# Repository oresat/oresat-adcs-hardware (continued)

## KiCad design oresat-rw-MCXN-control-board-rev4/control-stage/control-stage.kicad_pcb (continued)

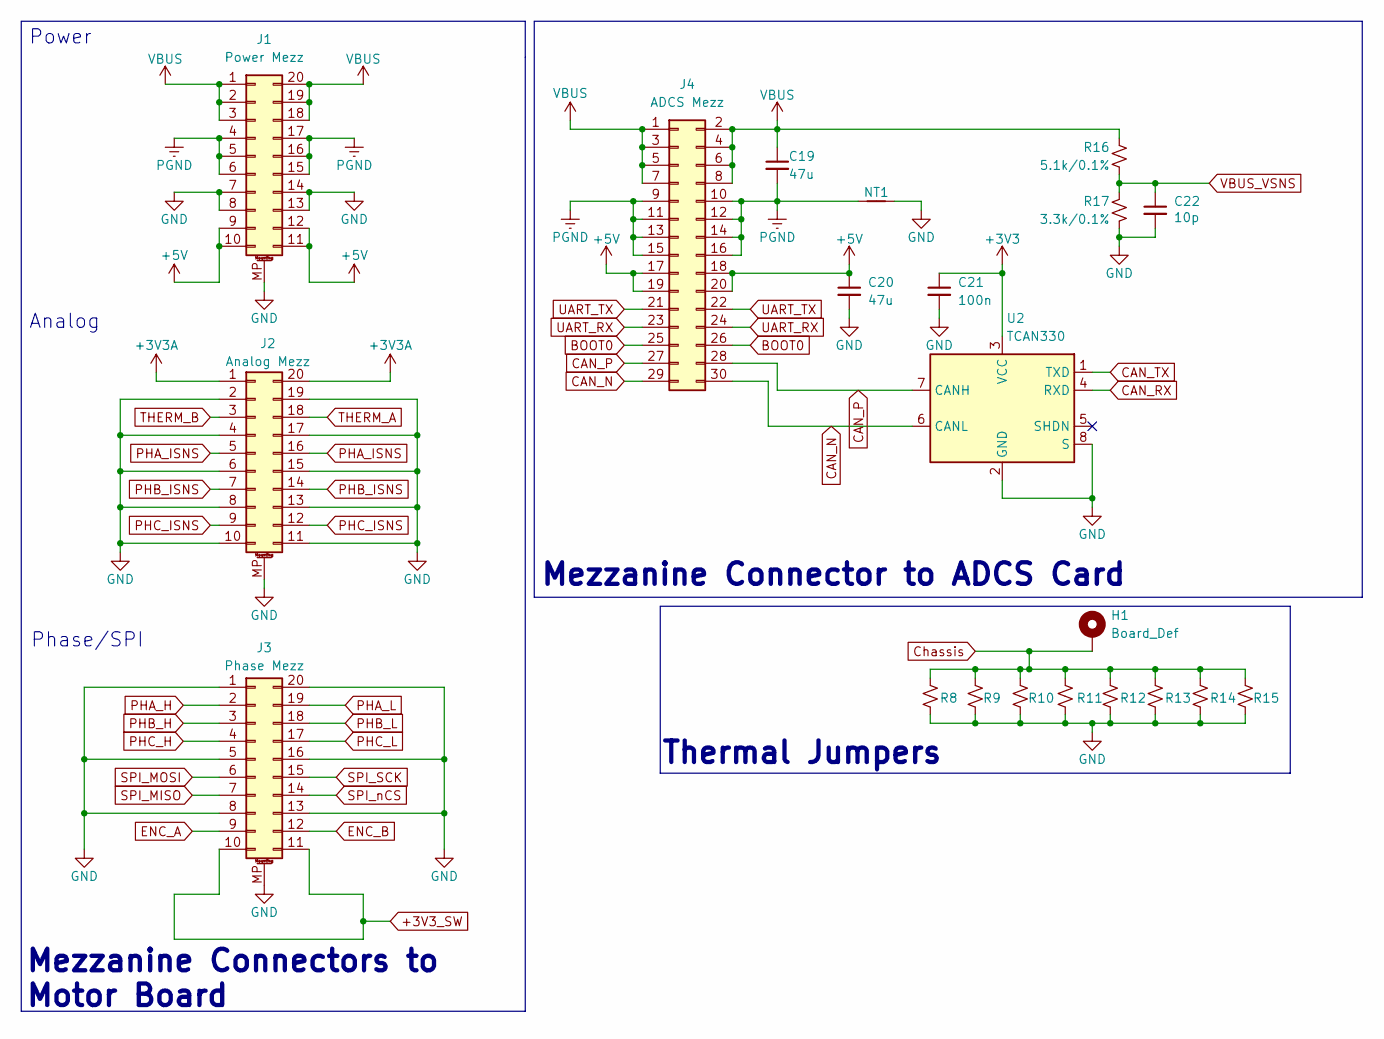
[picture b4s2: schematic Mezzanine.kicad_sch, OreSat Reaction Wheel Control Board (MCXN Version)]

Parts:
C19, C20: 47u; C_1210_3225Metric; Mfg P/N GRM32ER71A476KE15L
C21: 100n; C_0402_1005Metric; Mfg P/N GRM155R61A104KA01J
C22: 10p; C_0402_1005Metric; Mfg P/N GRM1555C1H100JA01D
H1: Board_Def; top-board-def-rev7.1
J1: Power Mezz; 10132798-021100LF; Mfg P/N 10132798-021100LF
J2: Analog Mezz; 10132798-021100LF; Mfg P/N 10132798-021100LF
J3: Phase Mezz; 10132798-021100LF; Mfg P/N 10132798-021100LF
J4: ADCS Mezz; 0555600307; Mfg P/N 555600307
NT1: NetTie; NetTie_ADCS
R8, R9, R10, R11, R12, R13, R14, R15: THJP1206ABT1; R_1206_3216Metric; Mfg P/N THJP1206ABT1
R16: 5.1k/0.1%; R_0402_1005Metric; Mfg P/N RP0402BRD075K1L
R17: 3.3k/0.1%; R_0402_1005Metric; Mfg P/N RP0402BRD073K3L
U2: TCAN330; SOT-23-8-Fixed; Mfg P/N TCAN330DCNR

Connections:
+3V3: C21.1, U2.3 (VCC); also elsewhere on the board
+3V3A: J2.1, J2.20; also elsewhere on the board
+3V3_SW: J3.10, J3.11; also elsewhere on the board
+5V: C20.1, J1.9, J1.10, J1.11, J1.12, J4.17, J4.18, J4.19, J4.20; also elsewhere on the board
BOOT0: J4.25, J4.26; also elsewhere on the board
CAN_N: J4.29, J4.30, U2.6 (CANL)
CAN_P: J4.27, J4.28, U2.7 (CANH)
CAN_RX: U2.4 (RXD); also elsewhere on the board
CAN_TX: U2.1 (TXD); also elsewhere on the board
Chassis: H1.1, R8.1, R9.1, R10.1, R11.1, R12.1, R13.1, R14.1, R15.1
ENC_A: J3.9; also elsewhere on the board
ENC_B: J3.12; also elsewhere on the board
GND: C20.2, C21.2, C22.2, J1.7, J1.8, J1.13, J1.14, J1.MP (MountPin), J2.2, J2.4, J2.6, J2.8, J2.10, J2.11, J2.13, J2.15, J2.17, J2.19, J2.MP (MountPin), J3.1, J3.5, J3.8, J3.13, J3.16, J3.20, J3.MP (MountPin), NT1.2, R8.2, R9.2, R10.2, R11.2, R12.2, R13.2, R14.2, R15.2, R17.1, U2.2 (GND), U2.8 (S); also elsewhere on the board
PGND: C19.2, J1.4, J1.5, J1.6, J1.15, J1.16, J1.17, J4.9, J4.10, J4.11, J4.12, J4.13, J4.14, J4.15, J4.16, NT1.1
PHA_H: J3.2; also elsewhere on the board
PHA_ISNS: J2.5, J2.16; also elsewhere on the board
PHA_L: J3.19; also elsewhere on the board
PHB_H: J3.3; also elsewhere on the board
PHB_ISNS: J2.7, J2.14; also elsewhere on the board
PHB_L: J3.18; also elsewhere on the board
PHC_H: J3.4; also elsewhere on the board
PHC_ISNS: J2.9, J2.12; also elsewhere on the board
PHC_L: J3.17; also elsewhere on the board
SPI_MISO: J3.7; also elsewhere on the board
SPI_MOSI: J3.6; also elsewhere on the board
SPI_SCK: J3.15; also elsewhere on the board
SPI_nCS: J3.14; also elsewhere on the board
THERM_A: J2.18; also elsewhere on the board
THERM_B: J2.3; also elsewhere on the board
UART_RX: J4.23, J4.24; also elsewhere on the board
UART_TX: J4.21, J4.22; also elsewhere on the board
VBUS: C19.1, J1.1, J1.2, J1.3, J1.18, J1.19, J1.20, J4.1, J4.2, J4.3, J4.4, J4.5, J4.6, J4.7, J4.8, R16.1
VBUS_VSNS: C22.1, R16.2, R17.2; also elsewhere on the board

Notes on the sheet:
Power
Mezzanine Connector to ADCS Card
Thermal Jumpers
Phase/SPI
Analog
Mezzanine Connectors to Motor Board

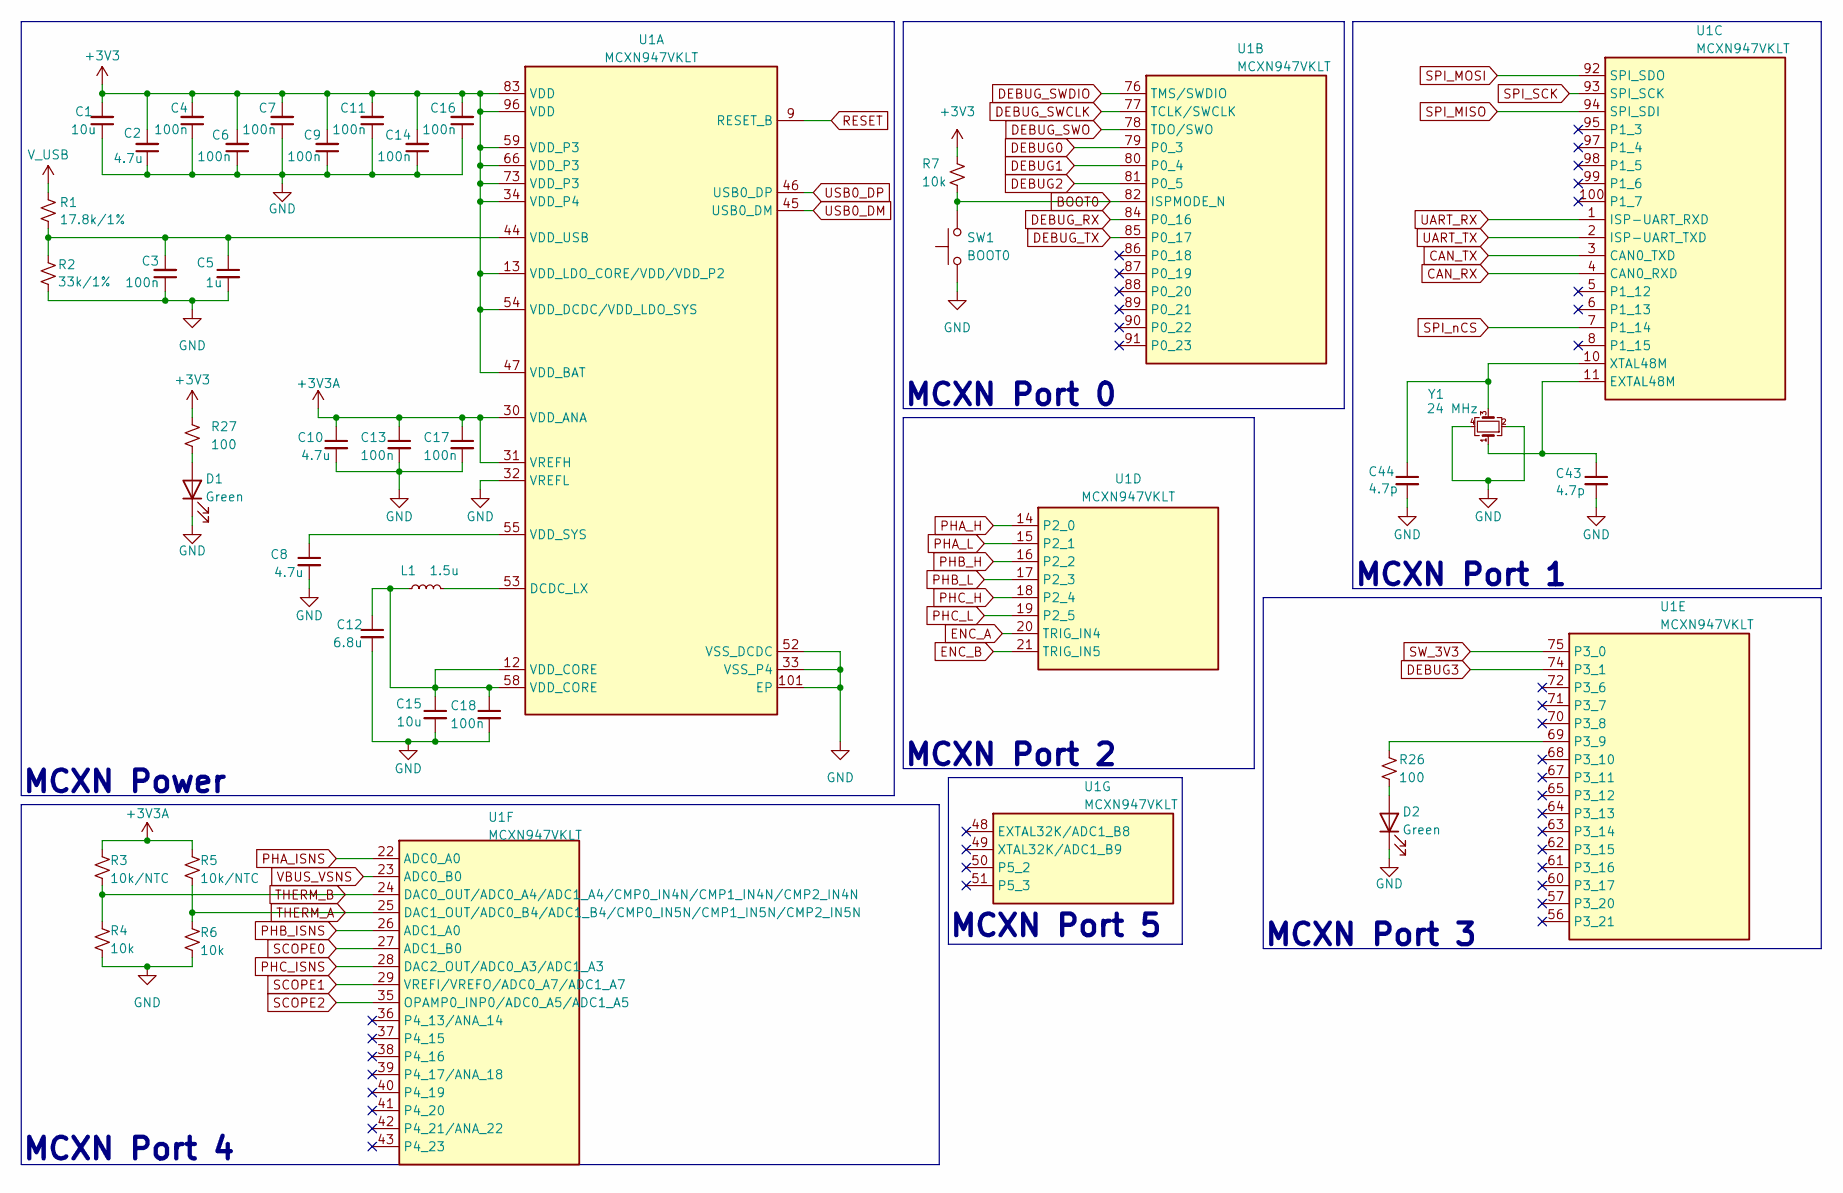
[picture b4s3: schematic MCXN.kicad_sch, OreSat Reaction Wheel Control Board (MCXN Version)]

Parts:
C1, C15: 10u; C_0603_1608Metric; Mfg P/N GRM188R61A106KE69J
C2, C8, C10: 4.7u; C_0603_1608Metric; Mfg P/N GRM185R61A475KE11D
C3, C4, C6, C7, C9, C11, C13, C14, C16, C17, C18: 100n; C_0402_1005Metric; Mfg P/N GRM155R61A104KA01J
C5: 1u; C_0402_1005Metric; Mfg P/N GRT155R61A105KE01D
C12: 6.8u; C_1206_3216Metric; Mfg P/N CGA5L1X7R1C685M160AC
C43, C44: 4.7p; 0603-C-NOSILK; MPN GRM1885C1H4R7WA01D
D1, D2: Green; LED_0603_1608Metric; Mfg P/N 150060VS55040
L1: 1.5u; L_0805_2012Metric; MPN SRP2012TMA-1R5M
R1: 17.8k/1%; R_0603_1608Metric; Mfg P/N ERJ-UP3F1782V
R2: 33k/1%; R_0603_1608Metric; Mfg P/N ERJ-UP3F3302V
R3, R5: 10k/NTC; R_0402_1005Metric; Mfg P/N NCU15XH103F6SRC
R4, R6, R7: 10k; R_0402_1005Metric; Mfg P/N AC0402DR-0710KL
R26, R27: 100; R_0402_1005Metric; Mfg P/N SR0402FR-7T100RL
SW1: BOOT0; SW_Push_SPST_NO_Alps_SKRK; Mfg P/N SKRKAGE020
U1: MCXN947VKLT; MCXN947KVLT-QFP50P1600X1600X160-101N; MPN MCXN947VKLT
Y1: 24 MHz; Crystal_SMD_2016-4Pin_2.0x1.6mm; MPN 830108212309

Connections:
+3V3: C1.2, C2.2, C4.2, C6.2, C7.2, C9.2, C11.2, C14.2, C16.2, R7.1, R27.1, U1.13 (VDD_LDO_CORE/VDD/VDD_P2), U1.34 (VDD_P4), U1.47 (VDD_BAT), U1.54 (VDD_DCDC/VDD_LDO_SYS), U1.59 (VDD_P3), U1.66 (VDD_P3), U1.73 (VDD_P3), U1.83 (VDD), U1.96 (VDD); also elsewhere on the board
+3V3A: C10.1, C13.1, C17.1, R3.1, R5.1, U1.30 (VDD_ANA), U1.31 (VREFH); also elsewhere on the board
BOOT0: R7.2, SW1.2, U1.82 (ISPMODE_N); also elsewhere on the board
CAN_RX: U1.4 (CAN0_RXD); also elsewhere on the board
CAN_TX: U1.3 (CAN0_TXD); also elsewhere on the board
DEBUG0: U1.79 (P0_3); also elsewhere on the board
DEBUG1: U1.80 (P0_4); also elsewhere on the board
DEBUG2: U1.81 (P0_5); also elsewhere on the board
DEBUG3: U1.74 (P3_1); also elsewhere on the board
DEBUG_RX: U1.84 (P0_16); also elsewhere on the board
DEBUG_SWCLK: U1.77 (TCLK/SWCLK); also elsewhere on the board
DEBUG_SWDIO: U1.76 (TMS/SWDIO); also elsewhere on the board
DEBUG_SWO: U1.78 (TDO/SWO); also elsewhere on the board
DEBUG_TX: U1.85 (P0_17); also elsewhere on the board
ENC_A: U1.20 (TRIG_IN4); also elsewhere on the board
ENC_B: U1.21 (TRIG_IN5); also elsewhere on the board
GND: C1.1, C2.1, C3.1, C4.1, C5.2, C6.1, C7.1, C8.2, C9.1, C10.2, C11.1, C12.2, C13.2, C14.1, C15.2, C16.1, C17.2, C18.2, C43.2, C44.2, D1.1 (K), D2.1 (K), R2.1, R4.2, R6.2, SW1.1, U1.32 (VREFL), U1.33 (VSS_P4), U1.52 (VSS_DCDC), U1.101 (EP), Y1.2, Y1.4; also elsewhere on the board
unnamed: C12.1, C15.1, C18.1, L1.1, U1.12 (VDD_CORE), U1.58 (VDD_CORE)
unnamed: D1.2 (A), R27.2
unnamed: D2.2 (A), R26.2
unnamed: L1.2, U1.53 (DCDC_LX)
unnamed: C8.1, U1.55 (VDD_SYS)
unnamed: C3.2, C5.1, R1.1, R2.2, U1.44 (VDD_USB)
unnamed: C44.1, U1.10 (XTAL48M), Y1.3
unnamed: C43.1, U1.11 (EXTAL48M), Y1.1
unnamed: R26.1, U1.69 (P3_9)
PHA_H: U1.14 (P2_0); also elsewhere on the board
PHA_ISNS: U1.22 (ADC0_A0); also elsewhere on the board
PHA_L: U1.15 (P2_1); also elsewhere on the board
PHB_H: U1.16 (P2_2); also elsewhere on the board
PHB_ISNS: U1.26 (ADC1_A0); also elsewhere on the board
PHB_L: U1.17 (P2_3); also elsewhere on the board
PHC_H: U1.18 (P2_4); also elsewhere on the board
PHC_ISNS: U1.28 (DAC2_OUT/ADC0_A3/ADC1_A3); also elsewhere on the board
PHC_L: U1.19 (P2_5); also elsewhere on the board
RESET: U1.9 (RESET_B); also elsewhere on the board
SCOPE0: U1.27 (ADC1_B0); also elsewhere on the board
SCOPE1: U1.29 (VREFI/VREFO/ADC0_A7/ADC1_A7); also elsewhere on the board
SCOPE2: U1.35 (OPAMP0_INP0/ADC0_A5/ADC1_A5); also elsewhere on the board
SPI_MISO: U1.94 (SPI_SDI); also elsewhere on the board
SPI_MOSI: U1.92 (SPI_SDO); also elsewhere on the board
SPI_SCK: U1.93 (SPI_SCK); also elsewhere on the board
SPI_nCS: U1.7 (P1_14); also elsewhere on the board
SW_3V3: U1.75 (P3_0); also elsewhere on the board
THERM_A: R5.2, R6.1, U1.25 (DAC1_OUT/ADC0_B4/ADC1_B4/CMP0_IN5N/CMP1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); also elsewhere on the board
THERM_B: R3.2, R4.1, U1.24 (DAC0_OUT/ADC0_A4/ADC1_A4/CMP0_IN4N/CMP1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); also elsewhere on the board
UART_RX: U1.1 (ISP-UART_RXD); also elsewhere on the board
UART_TX: U1.2 (ISP-UART_TXD); also elsewhere on the board
USB0_DM: U1.45 (USB0_DM); also elsewhere on the board
USB0_DP: U1.46 (USB0_DP); also elsewhere on the board
VBUS_VSNS: U1.23 (ADC0_B0); also elsewhere on the board
V_USB: R1.2; also elsewhere on the board

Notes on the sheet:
MCXN Port 3
MCXN Port 0
MCXN Port 4
MCXN Power
MCXN Port 1
MCXN Port 5
MCXN Port 2

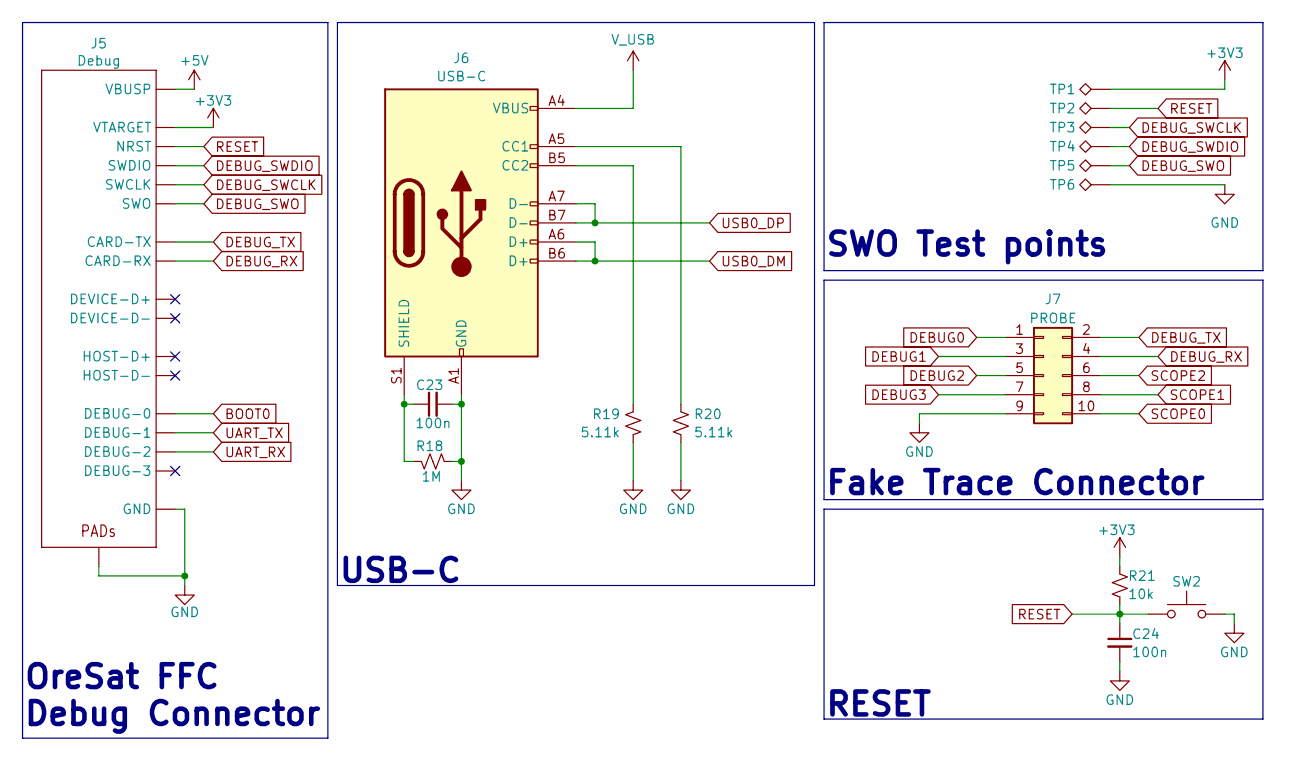
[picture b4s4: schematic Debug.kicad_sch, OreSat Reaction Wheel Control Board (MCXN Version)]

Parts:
C23, C24: 100n; C_0402_1005Metric; Mfg P/N GRM155R61A104KA01J
J5: Debug; J-TE_2-1734592-0; Mfg P/N 2-1734592-0
J6: USB-C; USB_C_Receptacle_Palconn_UTC16-G
J7: PROBE; PinHeader_2x05_P1.27mm_Horizontal; Mfg P/N FTSH-105-02-L-DV-A
R18: 1M; R_0805_2012Metric; Mfg P/N RCS08051M00FKEA
R19, R20: 5.11k; C_0603_1608Metric; Mfg P/N ERJ-UP3F5111V
R21: 10k; R_0402_1005Metric; Mfg P/N AC0402DR-0710KL
SW2: RESET; SW_Push_SPST_NO_Alps_SKRK; Mfg P/N SKRKAGE020
TP1, TP2, TP3, TP4, TP5, TP6: TestPoint_Alt; TestPoint_THTPad_1.0x1.0mm_Drill0.5mm

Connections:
+3V3: J5.11 (VTARGET), R21.2, TP1.1; also elsewhere on the board
+5V: J5.1 (VBUSP), J5.2 (VBUSP); also elsewhere on the board
BOOT0: J5.17 (DEBUG-0); also elsewhere on the board
DEBUG0: J7.1; also elsewhere on the board
DEBUG1: J7.3; also elsewhere on the board
DEBUG2: J7.5; also elsewhere on the board
DEBUG3: J7.7; also elsewhere on the board
DEBUG_RX: J5.12 (CARD-RX), J7.4; also elsewhere on the board
DEBUG_SWCLK: J5.15 (SWCLK), TP3.1; also elsewhere on the board
DEBUG_SWDIO: J5.14 (SWDIO), TP4.1; also elsewhere on the board
DEBUG_SWO: J5.16 (SWO), TP5.1; also elsewhere on the board
DEBUG_TX: J5.13 (CARD-TX), J7.2; also elsewhere on the board
GND: C23.2, C24.2, J5.3 (GND), J5.6 (GND), J5.9 (GND), J5.PAD1 (PAD), J5.PAD2 (PAD), J6.A1 (GND), J6.A12 (GND), J6.B1 (GND), J6.B12 (GND), J7.9, R18.1, R19.1, R20.1, SW2.2, TP6.1; also elsewhere on the board
unnamed: J6.A5 (CC1), R20.2
unnamed: J6.B5 (CC2), R19.2
unnamed: C23.1, J6.S1 (SHIELD), R18.2
RESET: C24.1, J5.10 (NRST), R21.1, SW2.1, TP2.1; also elsewhere on the board
SCOPE0: J7.10; also elsewhere on the board
SCOPE1: J7.8; also elsewhere on the board
SCOPE2: J7.6; also elsewhere on the board
UART_RX: J5.19 (DEBUG-2); also elsewhere on the board
UART_TX: J5.18 (DEBUG-1); also elsewhere on the board
USB0_DM: J6.A6 (D+), J6.B6 (D+); also elsewhere on the board
USB0_DP: J6.A7 (D-), J6.B7 (D-); also elsewhere on the board
V_USB: J6.A4 (VBUS), J6.A9 (VBUS), J6.B4 (VBUS), J6.B9 (VBUS); also elsewhere on the board

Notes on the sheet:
USB-C
Fake Trace Connector
OreSat FFC Debug Connector
SWO Test points
RESET

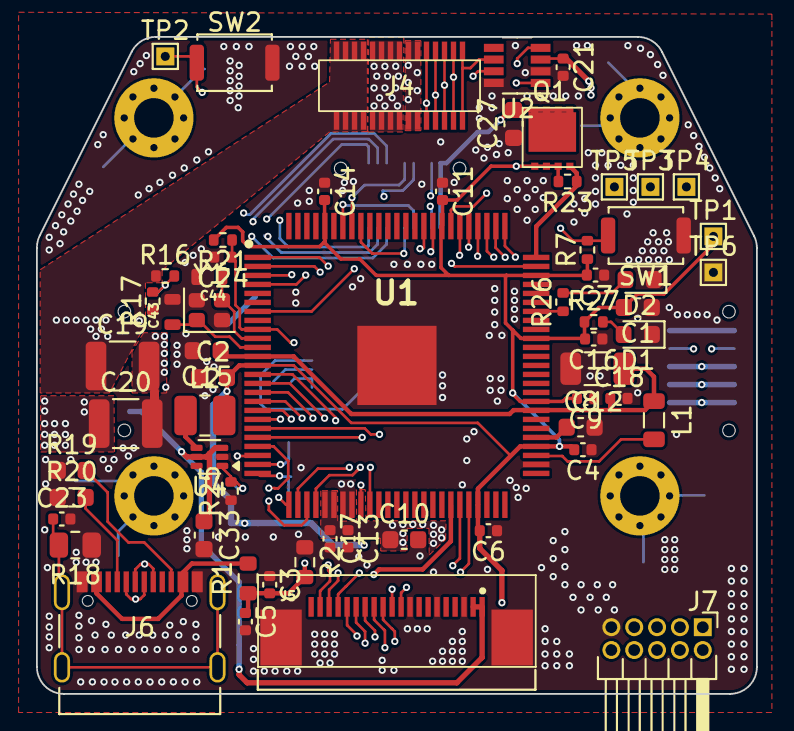
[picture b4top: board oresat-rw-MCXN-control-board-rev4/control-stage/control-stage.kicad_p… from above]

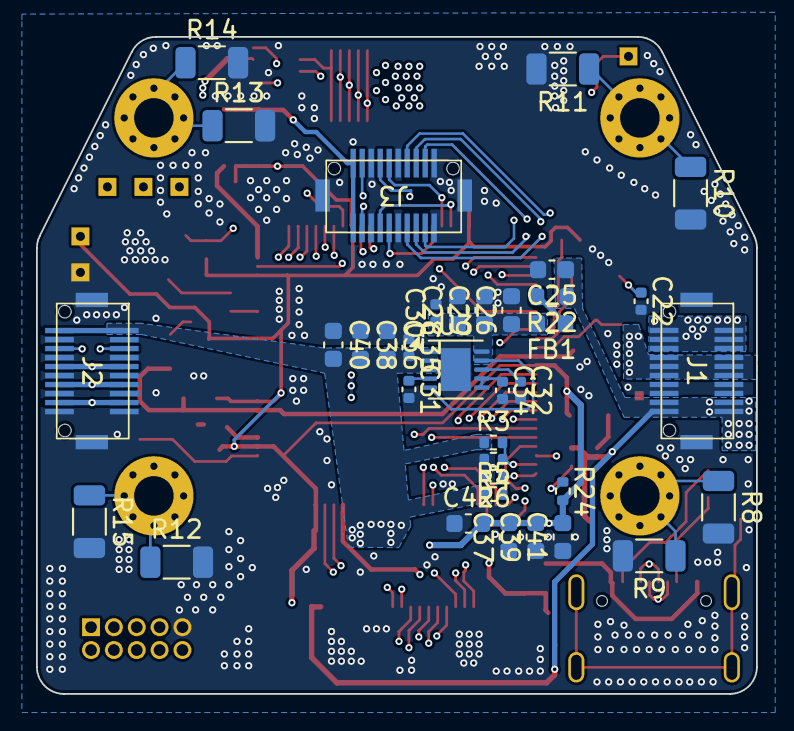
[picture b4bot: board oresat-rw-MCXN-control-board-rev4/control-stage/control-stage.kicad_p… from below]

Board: 6 copper layers, 40.0 x 36.5 mm, 99 parts (36 on the bottom side), 69 nets.

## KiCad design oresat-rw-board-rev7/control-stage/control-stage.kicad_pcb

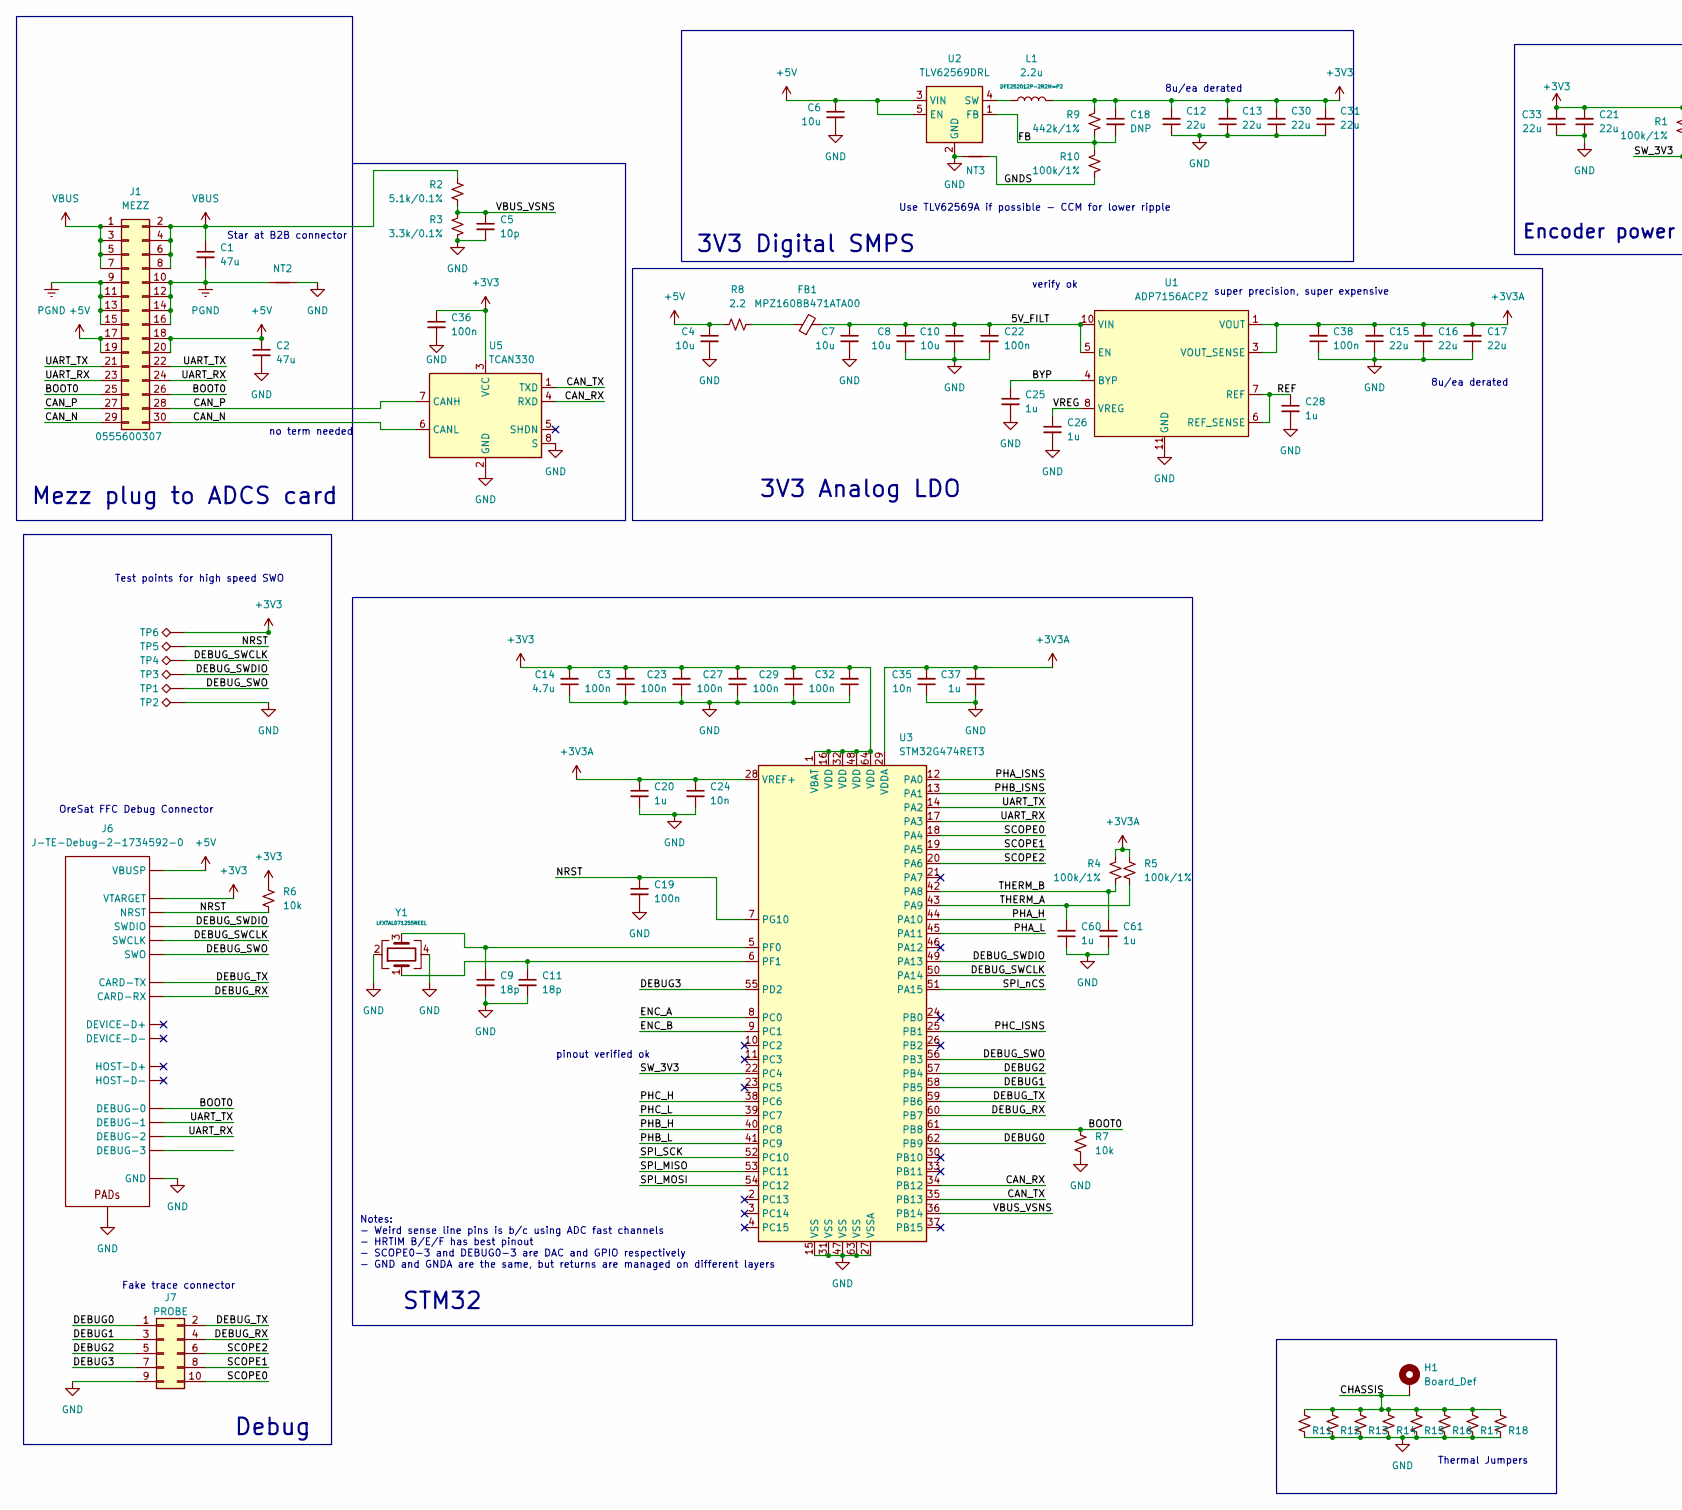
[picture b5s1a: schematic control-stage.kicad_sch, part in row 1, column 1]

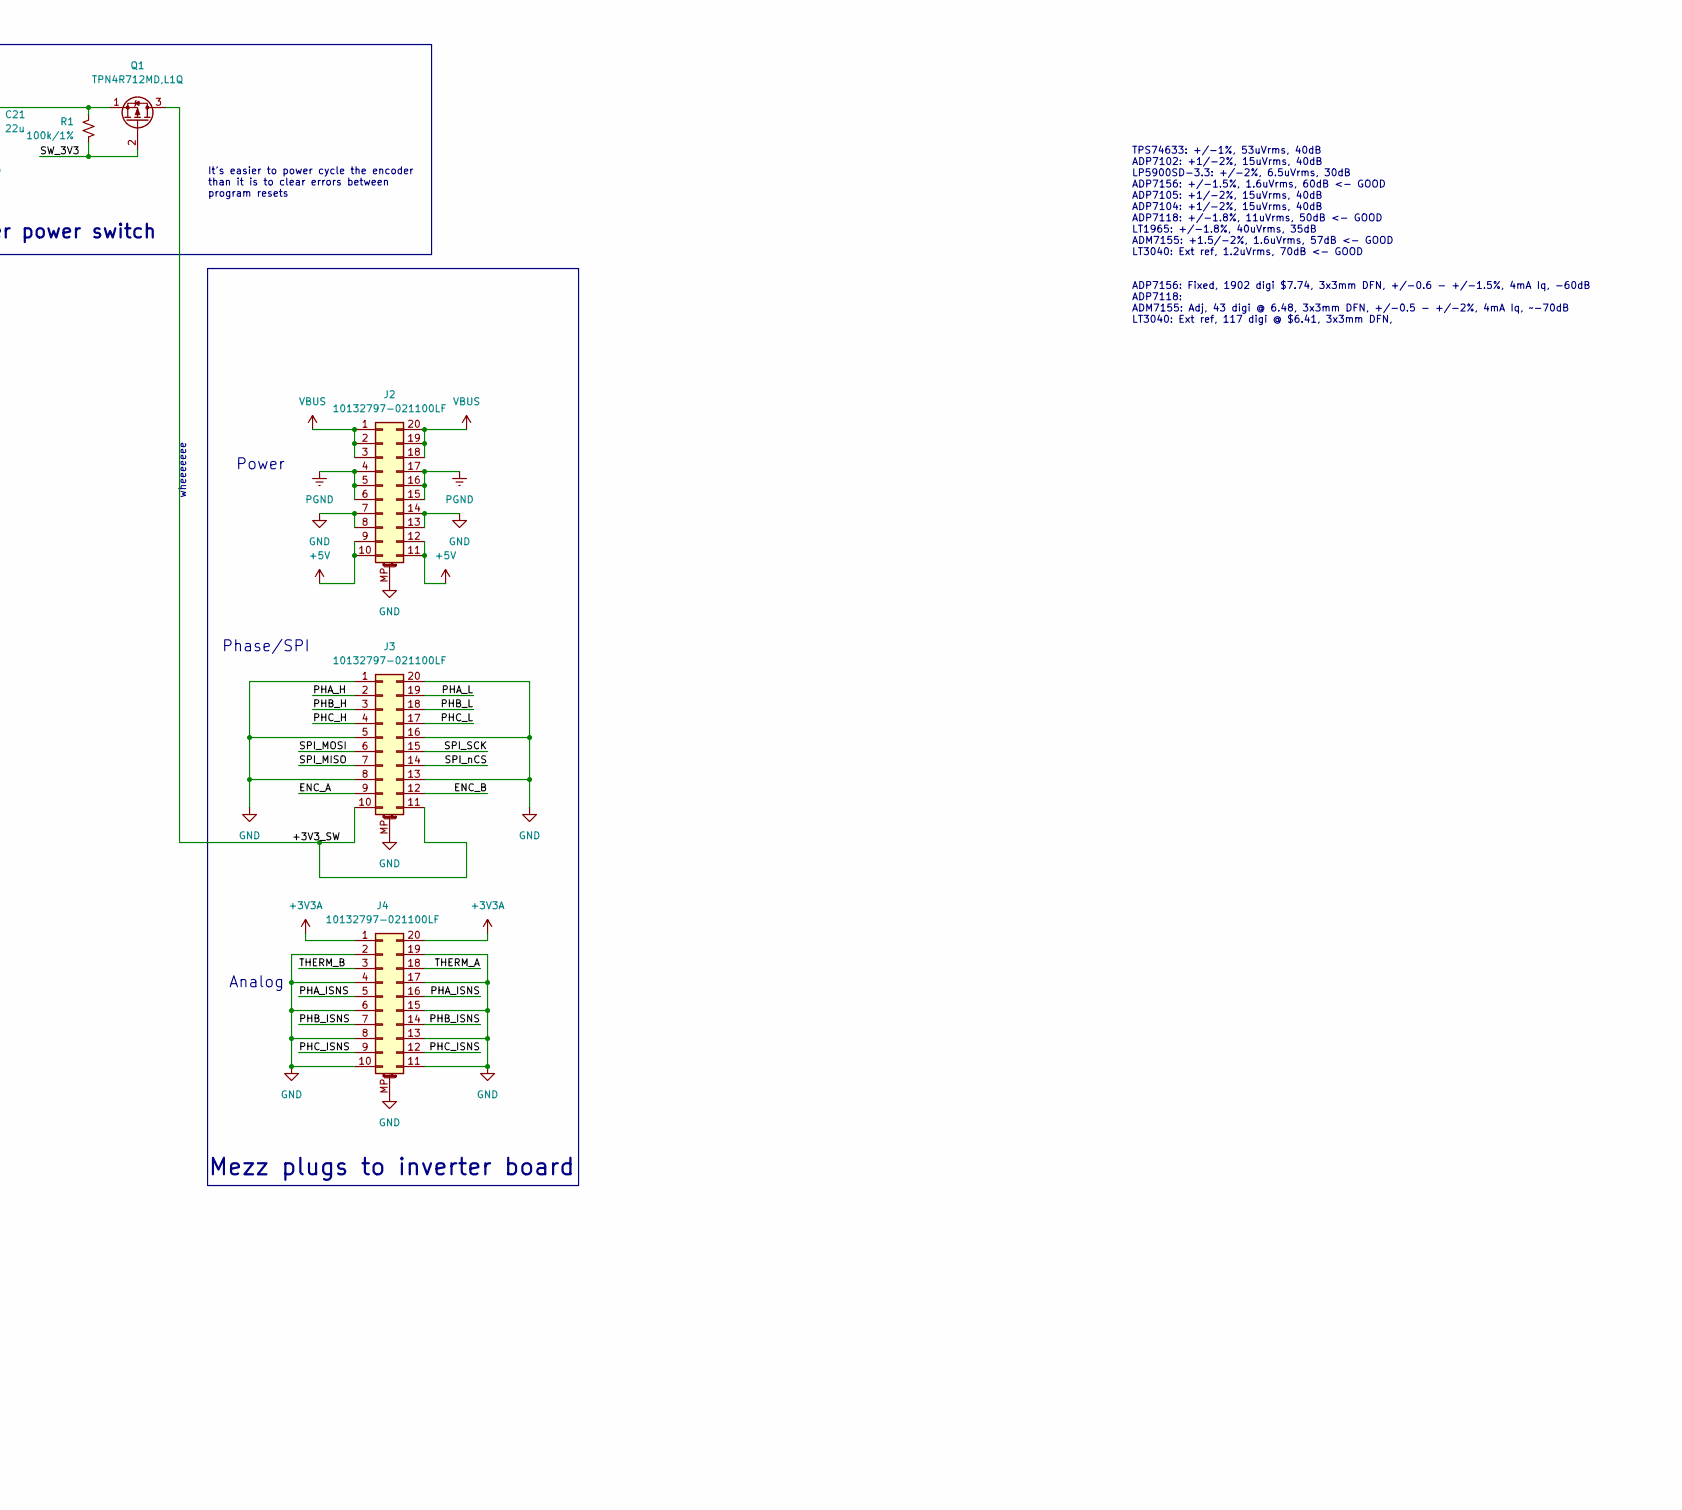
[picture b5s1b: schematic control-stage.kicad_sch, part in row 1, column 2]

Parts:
C1, C2: 47u; C_1210_3225Metric
C3, C19, C22, C23, C27, C29, C32, C36, C38: 100n; C_0402_1005Metric
C4, C6, C7, C8, C10: 10u; C_0603_1608Metric
C5: 10p; C_0402_1005Metric
C9, C11: 18p; C_0402_1005Metric
C12, C13, C15, C16, C17, C21, C30, C31, C33: 22u; C_0603_1608Metric
C14: 4.7u; C_0603_1608Metric
C18: DNP; C_0402_1005Metric
C20, C25, C26, C28, C37, C60, C61: 1u; C_0402_1005Metric
C24, C35: 10n; C_0402_1005Metric
FB1: MPZ1608B471ATA00; L_0603_1608Metric
H1: Board_Def; top-board-def-rev7.1
J1: MEZZ; 0555600307
J2, J3, J4: 10132797-021100LF; 10132798-021100LF
J6: J-TE-Debug-2-1734592-0; J-TE_2-1734592-0
J7: PROBE; PinHeader_2x05_P1.27mm_Horizontal
L1: 2.2u; L_1008_2520Metric
NT2, NT3: NetTie_2; NetTie-2_SMD_Pad0.5mm
Q1: TPN4R712MD,L1Q; TSON-Advance
R1, R4, R5, R10: 100k/1%; R_0402_1005Metric
R2: 5.1k/0.1%; R_0402_1005Metric
R3: 3.3k/0.1%; R_0402_1005Metric
R6, R7: 10k; R_0402_1005Metric
R8: 2.2; R_0603_1608Metric
R9: 442k/1%; R_0402_1005Metric
R11, R12, R13, R14, R15, R16, R17, R18: THJP1206ABT1; R_1206_3216Metric
TP1, TP2, TP3, TP4, TP5, TP6: TestPoint_Alt; TestPoint_THTPad_1.0x1.0mm_Drill0.5mm
U1: ADP7156ACPZ; DFN-10-1EP_3x3mm_P0.5mm_EP1.65x2.38mm
U2: TLV62569DRL; SOT-563
U3: STM32G474RET3; LQFP-64_10x10mm_P0.5mm
U5: TCAN330; SOT-23-8-Fixed
Y1: Crystal_GND24; Crystal_SMD_2016-4Pin_2.0x1.6mm

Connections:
+3V3: C3.2, C12.2, C13.2, C14.2, C18.1, C21.2, C23.2, C27.2, C29.2, C30.2, C31.2, C32.2, C33.2, C36.1, J6.11 (VTARGET), L1.2, Q1.1 (S), R1.2, R6.1, R9.2, TP6.1, U3.1 (VBAT), U3.16 (VDD), U3.32 (VDD), U3.48 (VDD), U3.64 (VDD), U5.3 (VCC)
+3V3A: C15.2, C16.2, C17.2, C20.1, C24.1, C35.2, C37.2, C38.2, J4.1, J4.20, R4.2, R5.1, U1.1 (VOUT), U1.2 (VOUT), U1.3 (VOUT_SENSE), U3.28 (VREF+), U3.29 (VDDA)
+5V: C2.1, C4.1, C6.1, J1.17, J1.18, J1.19, J1.20, J2.9, J2.10, J2.11, J2.12, J6.1 (VBUSP), J6.2 (VBUSP), R8.1, U2.3 (VIN), U2.5 (EN)
/5V_FILT: C7.1, C8.1, C10.1, C22.1, FB1.2, U1.5 (EN), U1.9 (VIN), U1.10 (VIN)
/+3V3_SW: J3.10, J3.11, Q1.3 (D)
/BOOT0: J1.25, J1.26, J6.17 (DEBUG-0), R7.1, U3.61 (PB8)
/BYP: C25.1, U1.4 (BYP)
/CAN_N: J1.29, J1.30, U5.6 (CANL)
/CAN_P: J1.27, J1.28, U5.7 (CANH)
/CAN_RX: U3.34 (PB12), U5.4 (RXD)
/CAN_TX: U3.35 (PB13), U5.1 (TXD)
/CHASSIS: H1.1, R11.1, R12.1, R13.1, R14.1, R15.1, R16.1, R17.1, R18.1
/DEBUG0: J7.1, U3.62 (PB9)
/DEBUG1: J7.3, U3.58 (PB5)
/DEBUG2: J7.5, U3.57 (PB4)
/DEBUG3: J7.7, U3.55 (PD2)
/DEBUG_RX: J6.12 (CARD-RX), J7.4, U3.60 (PB7)
/DEBUG_SWCLK: J6.15 (SWCLK), TP4.1, U3.50 (PA14)
/DEBUG_SWDIO: J6.14 (SWDIO), TP3.1, U3.49 (PA13)
/DEBUG_SWO: J6.16 (SWO), TP1.1, U3.56 (PB3)
/DEBUG_TX: J6.13 (CARD-TX), J7.2, U3.59 (PB6)
/ENC_A: J3.9, U3.8 (PC0)
/ENC_B: J3.12, U3.9 (PC1)
/FB: C18.2, R9.1, R10.2, U2.1 (FB)
/GNDS: NT3.2, R10.1
/NRST: C19.1, J6.10 (NRST), R6.2, TP5.1, U3.7 (PG10)
/PHA_H: J3.2, U3.44 (PA10)
/PHA_ISNS: J4.5, J4.16, U3.12 (PA0)
/PHA_L: J3.19, U3.45 (PA11)
/PHB_H: J3.3, U3.40 (PC8)
/PHB_ISNS: J4.7, J4.14, U3.13 (PA1)
/PHB_L: J3.18, U3.41 (PC9)
/PHC_H: J3.4, U3.38 (PC6)
/PHC_ISNS: J4.9, J4.12, U3.25 (PB1)
/PHC_L: J3.17, U3.39 (PC7)
/REF: C28.1, U1.6 (REF_SENSE), U1.7 (REF)
/SCOPE0: J7.10, U3.18 (PA4)
/SCOPE1: J7.8, U3.19 (PA5)
/SCOPE2: J7.6, U3.20 (PA6)
/SPI_MISO: J3.7, U3.53 (PC11)
/SPI_MOSI: J3.6, U3.54 (PC12)
/SPI_SCK: J3.15, U3.52 (PC10)
/SPI_nCS: J3.14, U3.51 (PA15)
/SW_3V3: Q1.2 (G), R1.1, U3.22 (PC4)
/THERM_A: J4.18, R5.2, U3.43 (PA9); also elsewhere on the board
/THERM_B: J4.3, R4.1, U3.42 (PA8); also elsewhere on the board
/UART_RX: J1.23, J1.24, J6.19 (DEBUG-2), U3.17 (PA3)
/UART_TX: J1.21, J1.22, J6.18 (DEBUG-1), U3.14 (PA2)
/VBUS_VSNS: C5.1, R2.2, R3.2, U3.36 (PB14)
/VREG: C26.1, U1.8 (VREG)
GND: C2.2, C3.1, C4.2, C5.2, C6.2, C7.2, C8.2, C9.2, C10.2, C11.2, C12.1, C13.1, C14.1, C15.1, C16.1, C17.1, C19.2, C20.2, C21.1, C22.2, C23.1, C24.2, C25.2, C26.2, C27.1, C28.2, C29.1, C30.1, C31.1, C32.1, C33.1, C35.1, C36.2, C37.1, C38.1, J2.7, J2.8, J2.13, J2.14, J2.MP (MountPin), J3.1, J3.5, J3.8, J3.13, J3.16, J3.20, J3.MP (MountPin), J4.2, J4.4, J4.6, J4.8, J4.10, J4.11, J4.13, J4.15, J4.17, J4.19, J4.MP (MountPin), J6.3 (GND), J6.6 (GND), J6.9 (GND), J6.PAD1 (PAD), J6.PAD2 (PAD), J7.9, NT2.2, NT3.1, R3.1, R7.2, R11.2, R12.2, R13.2, R14.2, R15.2, R16.2, R17.2, R18.2, TP2.1, U1.11 (GND), U2.2 (GND), U3.15 (VSS), U3.27 (VSSA), U3.31 (VSS), U3.47 (VSS), U3.63 (VSS), U5.2 (GND), U5.8 (S), Y1.2, Y1.4; also elsewhere on the board
unnamed: FB1.1, R8.2
unnamed: L1.1, U2.4 (SW)
unnamed: C9.1, U3.5 (PF0), Y1.3
unnamed: C11.1, U3.6 (PF1), Y1.1
PGND: C1.2, J1.9, J1.10, J1.11, J1.12, J1.13, J1.14, J1.15, J1.16, J2.4, J2.5, J2.6, J2.15, J2.16, J2.17, NT2.1
VBUS: C1.1, J1.1, J1.2, J1.3, J1.4, J1.5, J1.6, J1.7, J1.8, J2.1, J2.2, J2.3, J2.18, J2.19, J2.20, R2.1

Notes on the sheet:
Notes: - Weird sense line pins is b/c using ADC fast channels - HRTIM B/E/F has best pinout - SCOPE0-3 and DEBUG0-3 are DAC and GPIO respectively - GND and GNDA are the same, but returns are managed on different layers
8u/ea derated
Debug
Fake trace connector
Encoder power switch
Mezz plug to ADCS card
Use TLV62569A if possible - CCM for lower ripple
super precision, super expensive
OreSat FFC Debug Connector
Star at B2B connector
Test points for high speed SWO
TPS74633: +/-1%, 53uVrms, 40dB ADP7102: +1/-2%, 15uVrms, 40dB LP5900SD-3.3: +/-2%, 6.5uVrms, 30dB ADP7156: +/-1.5%, 1.6uVrms, 60dB <- GOOD ADP7105: +1/-2%, 15uVrms, 40dB ADP7104: +1/-2%, 15uVrms, 40dB ADP7118: +/-1.8%, 11uVrms, 50dB <- GOOD LT1965: +/-1.8%, 40uVrms, 35dB ADM7155: +1.5/-2%, 1.6uVrms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
3V3 Digital SMPS
Mezz plugs to inverter board
3V3 Analog LDO
Phase/SPI
verify ok
no term needed
STM32
pinout verified ok
Power
Thermal Jumpers
wheeeeeee
It's easier to power cycle the encoder than it is to clear errors between program resets
Analog

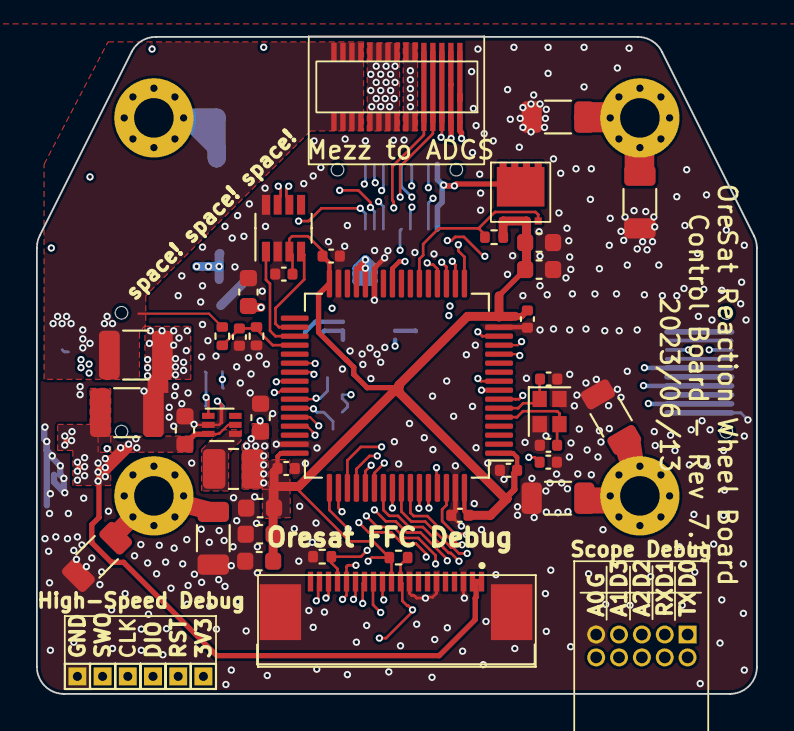
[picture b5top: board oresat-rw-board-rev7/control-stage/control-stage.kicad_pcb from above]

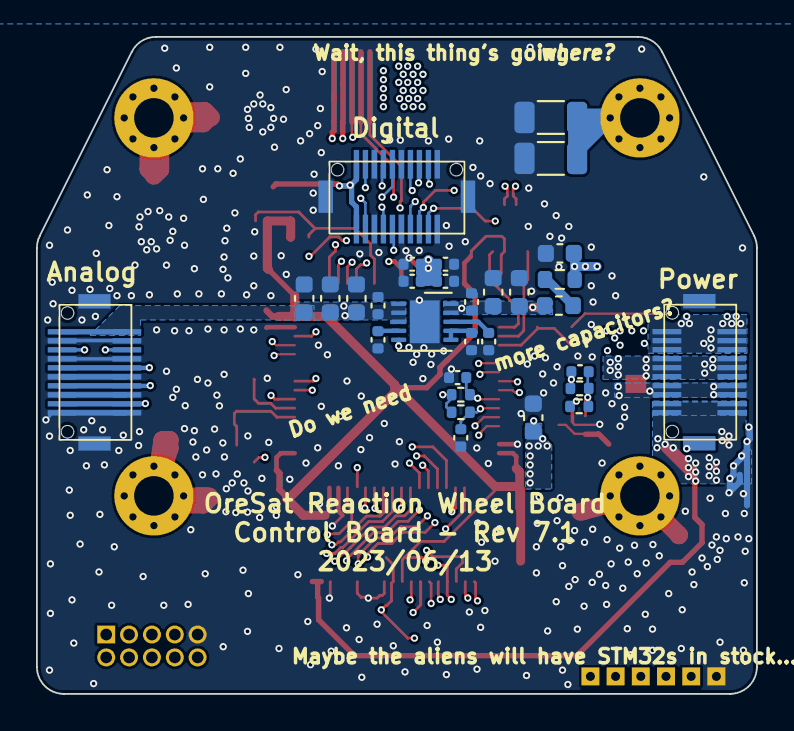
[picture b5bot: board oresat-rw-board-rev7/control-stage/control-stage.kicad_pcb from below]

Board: 6 copper layers, 40.0 x 36.5 mm, 80 parts (31 on the bottom side), 57 nets.

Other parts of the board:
C34, C39: 1u; C_0402_1005Metric

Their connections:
/THERM_A: C34.2; also elsewhere on the board
/THERM_B: C39.2; also elsewhere on the board
GND: C34.1, C39.1; also elsewhere on the board

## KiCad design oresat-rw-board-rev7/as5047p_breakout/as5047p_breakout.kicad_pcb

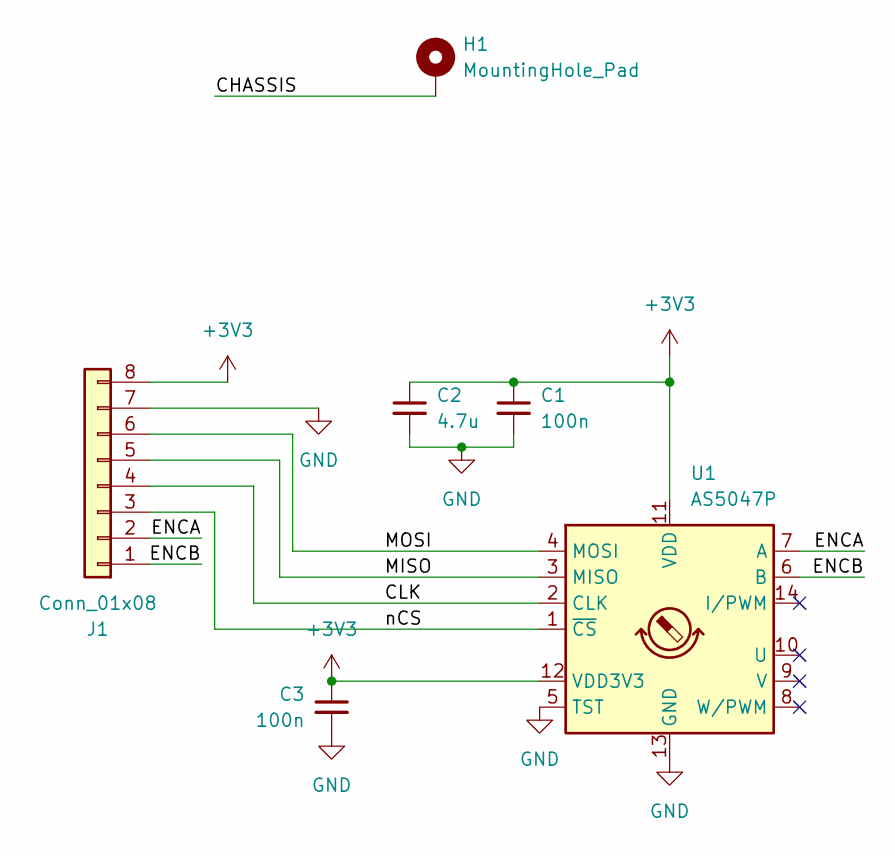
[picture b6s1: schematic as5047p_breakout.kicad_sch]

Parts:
C1, C3: 100n; C_0603_1608Metric
C2: 4.7u; C_0603_1608Metric
H1: MountingHole_Pad; board-def-rev7.2
J1: Conn_01x08; PinHeader_1x08_P2.54mm_Horizontal
U1: AS5047P; TSSOP-14_4.4x5mm_P0.65mm

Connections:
+3V3: C1.1, C2.1, C3.1, J1.8, U1.11 (VDD), U1.12 (VDD3V3)
/CHASSIS: H1.1
/CLK: J1.4, U1.2 (CLK)
/ENCA: J1.2, U1.7 (A)
/ENCB: J1.1, U1.6 (B)
/MISO: J1.5, U1.3 (MISO)
/MOSI: J1.6, U1.4 (MOSI)
/nCS: J1.3, U1.1 (~CS)
GND: C1.2, C2.2, C3.2, J1.7, U1.5 (TST), U1.13 (GND)
